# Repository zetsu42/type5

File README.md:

# type5

Pcb created with Kicad for sun type 5 keyboard.

You need 2 ffc/fpc connector, pitch 1.25 mm, 9 pole and 26 pole. I use molex's serie 52045.

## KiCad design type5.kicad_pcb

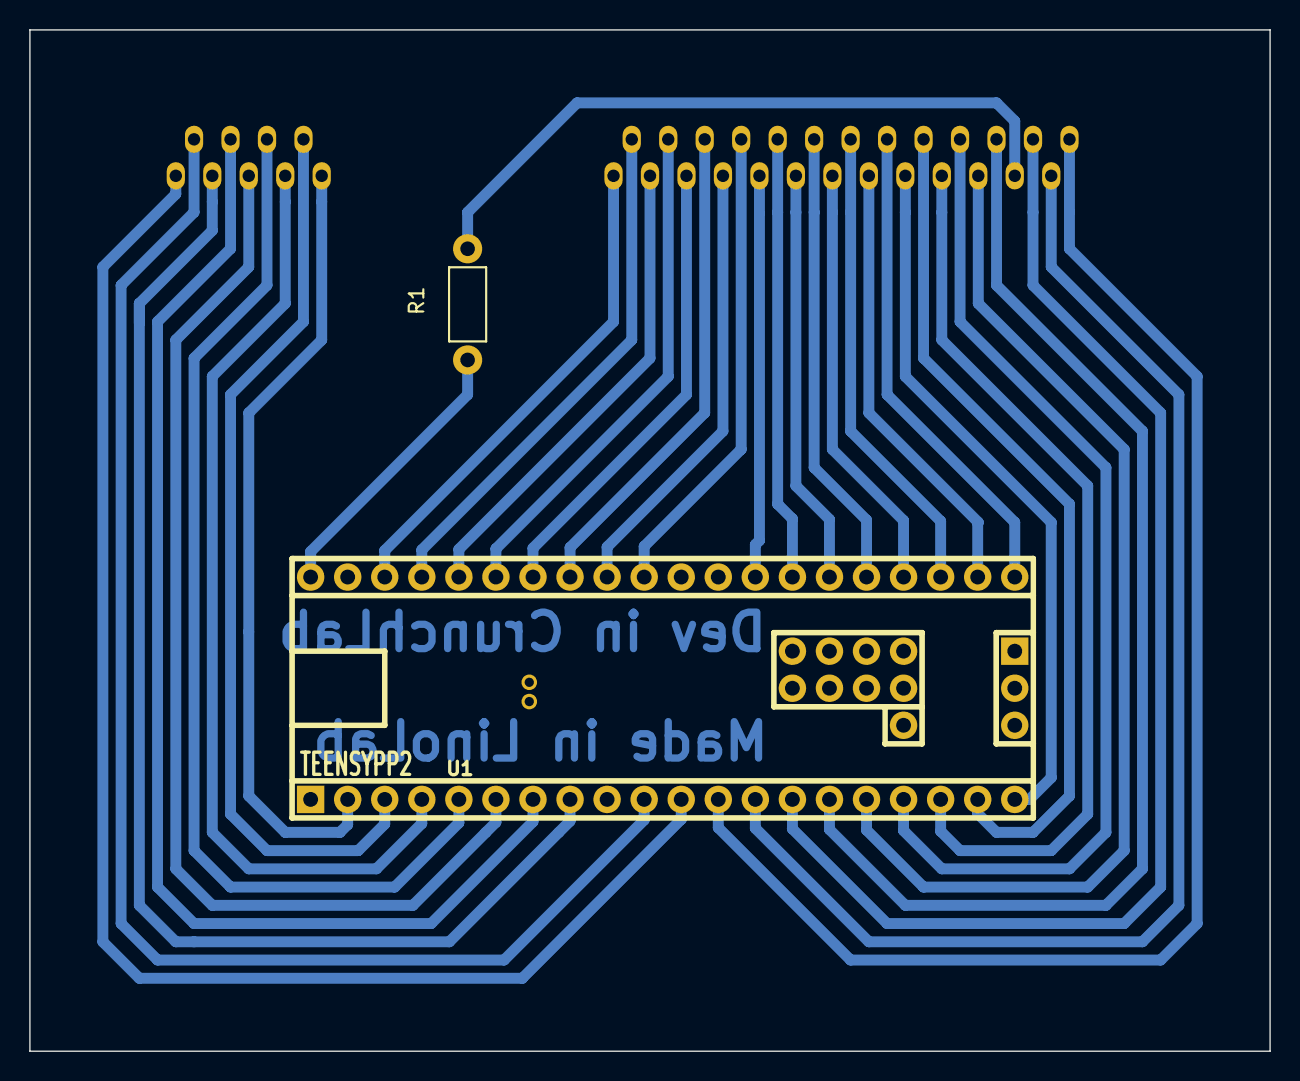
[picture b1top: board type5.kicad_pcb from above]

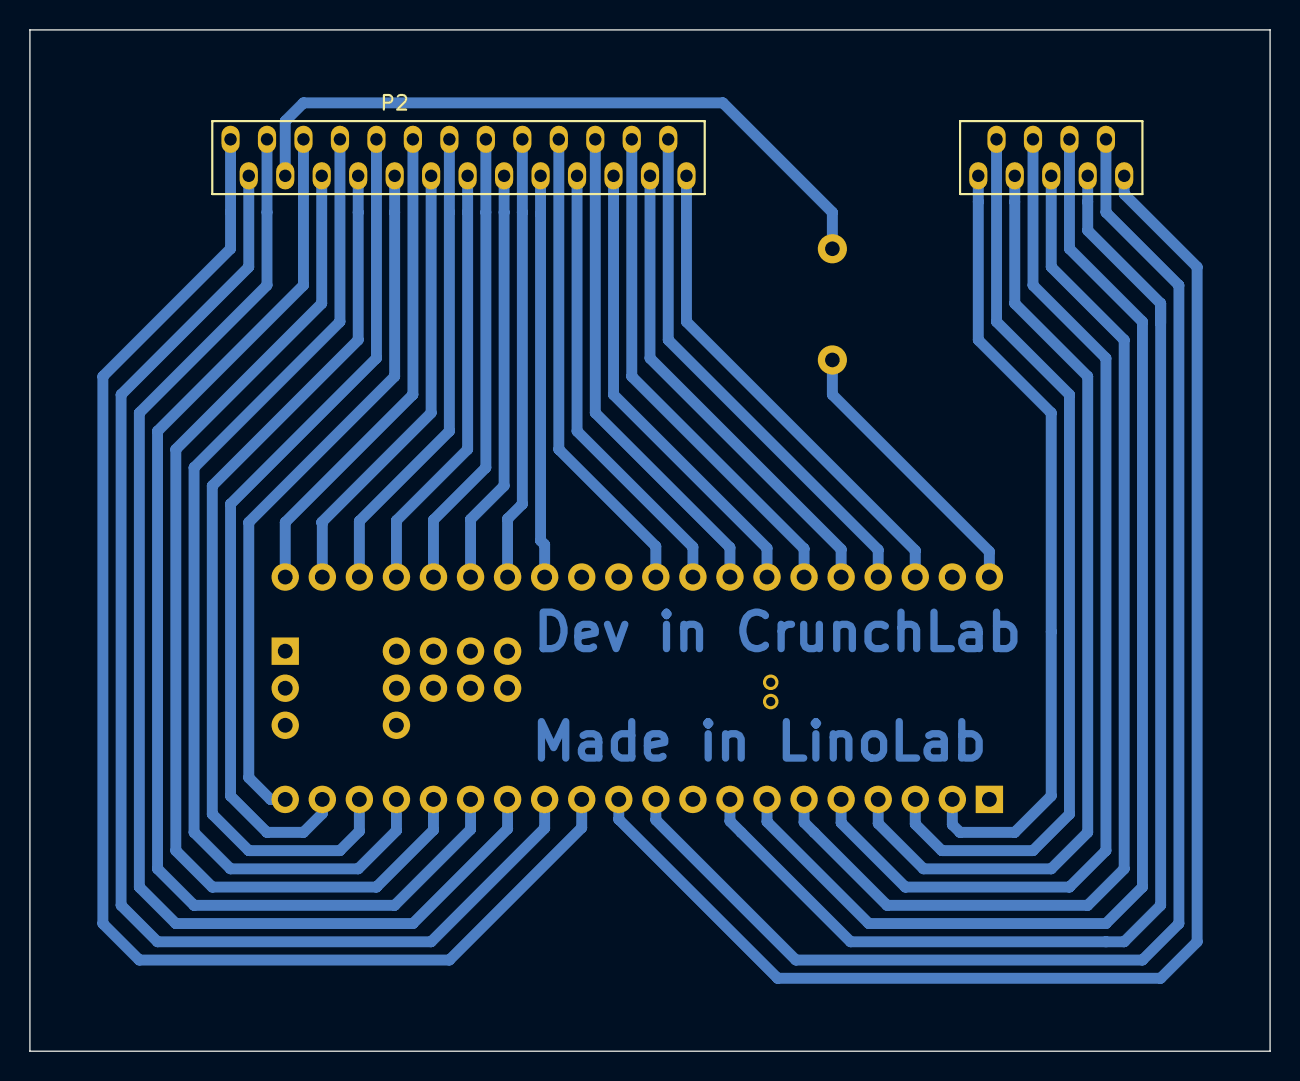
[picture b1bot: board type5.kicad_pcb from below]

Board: 2 copper layers, 85.0 x 70.0 mm, 4 parts (2 on the bottom side), 36 nets.

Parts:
P1: CONN_01X09; ffc_1.25mm_9p_oval
P2: CONN_01X26; ffc_1.25m_26p_oval
R1: R; Resistor_Horizontal_RM7mm
U1: TEENSYPP2

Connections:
unnamed: P1.1, U1.11
unnamed: P1.2, U1.10
unnamed: P1.3, U1.8
unnamed: P1.4, U1.7
unnamed: P1.5, U1.6
unnamed: P1.6, U1.5
unnamed: P1.7, U1.4
unnamed: P1.8, U1.3
unnamed: P1.9, U1.2
unnamed: P2.1, U1.50
unnamed: P2.2, U1.49
unnamed: P2.3, U1.48
unnamed: P2.4, U1.47
unnamed: P2.5, U1.46
unnamed: P2.6, U1.45
unnamed: P2.7, U1.44
unnamed: P2.8, U1.43
unnamed: P2.9, U1.40
unnamed: P2.10, U1.39
unnamed: P2.11, U1.38
unnamed: P2.12, U1.37
unnamed: P2.13, U1.36
unnamed: P2.14, U1.35
unnamed: P2.15, U1.34
unnamed: P2.16, U1.33
unnamed: P2.17, U1.20
unnamed: P2.18, U1.19
unnamed: P2.19, U1.18
unnamed: P2.20, U1.17
unnamed: P2.21, U1.16
unnamed: P2.22, U1.15
unnamed: P2.23, R1.2
unnamed: P2.24, U1.14
unnamed: P2.25, U1.13
unnamed: P2.26, U1.12
unnamed: R1.1, U1.52

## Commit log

2016-05-01 added matrix.ods
2016-05-01 pcb mod
2016-05-02 pcb mod and drill
2016-05-03 adsù
2016-05-04 new pcb
2016-05-06 fix, d6 unused
2016-05-06 mod odt
2016-05-06 ods guide
2016-05-12 finish (hope)
2016-05-23 new readme
